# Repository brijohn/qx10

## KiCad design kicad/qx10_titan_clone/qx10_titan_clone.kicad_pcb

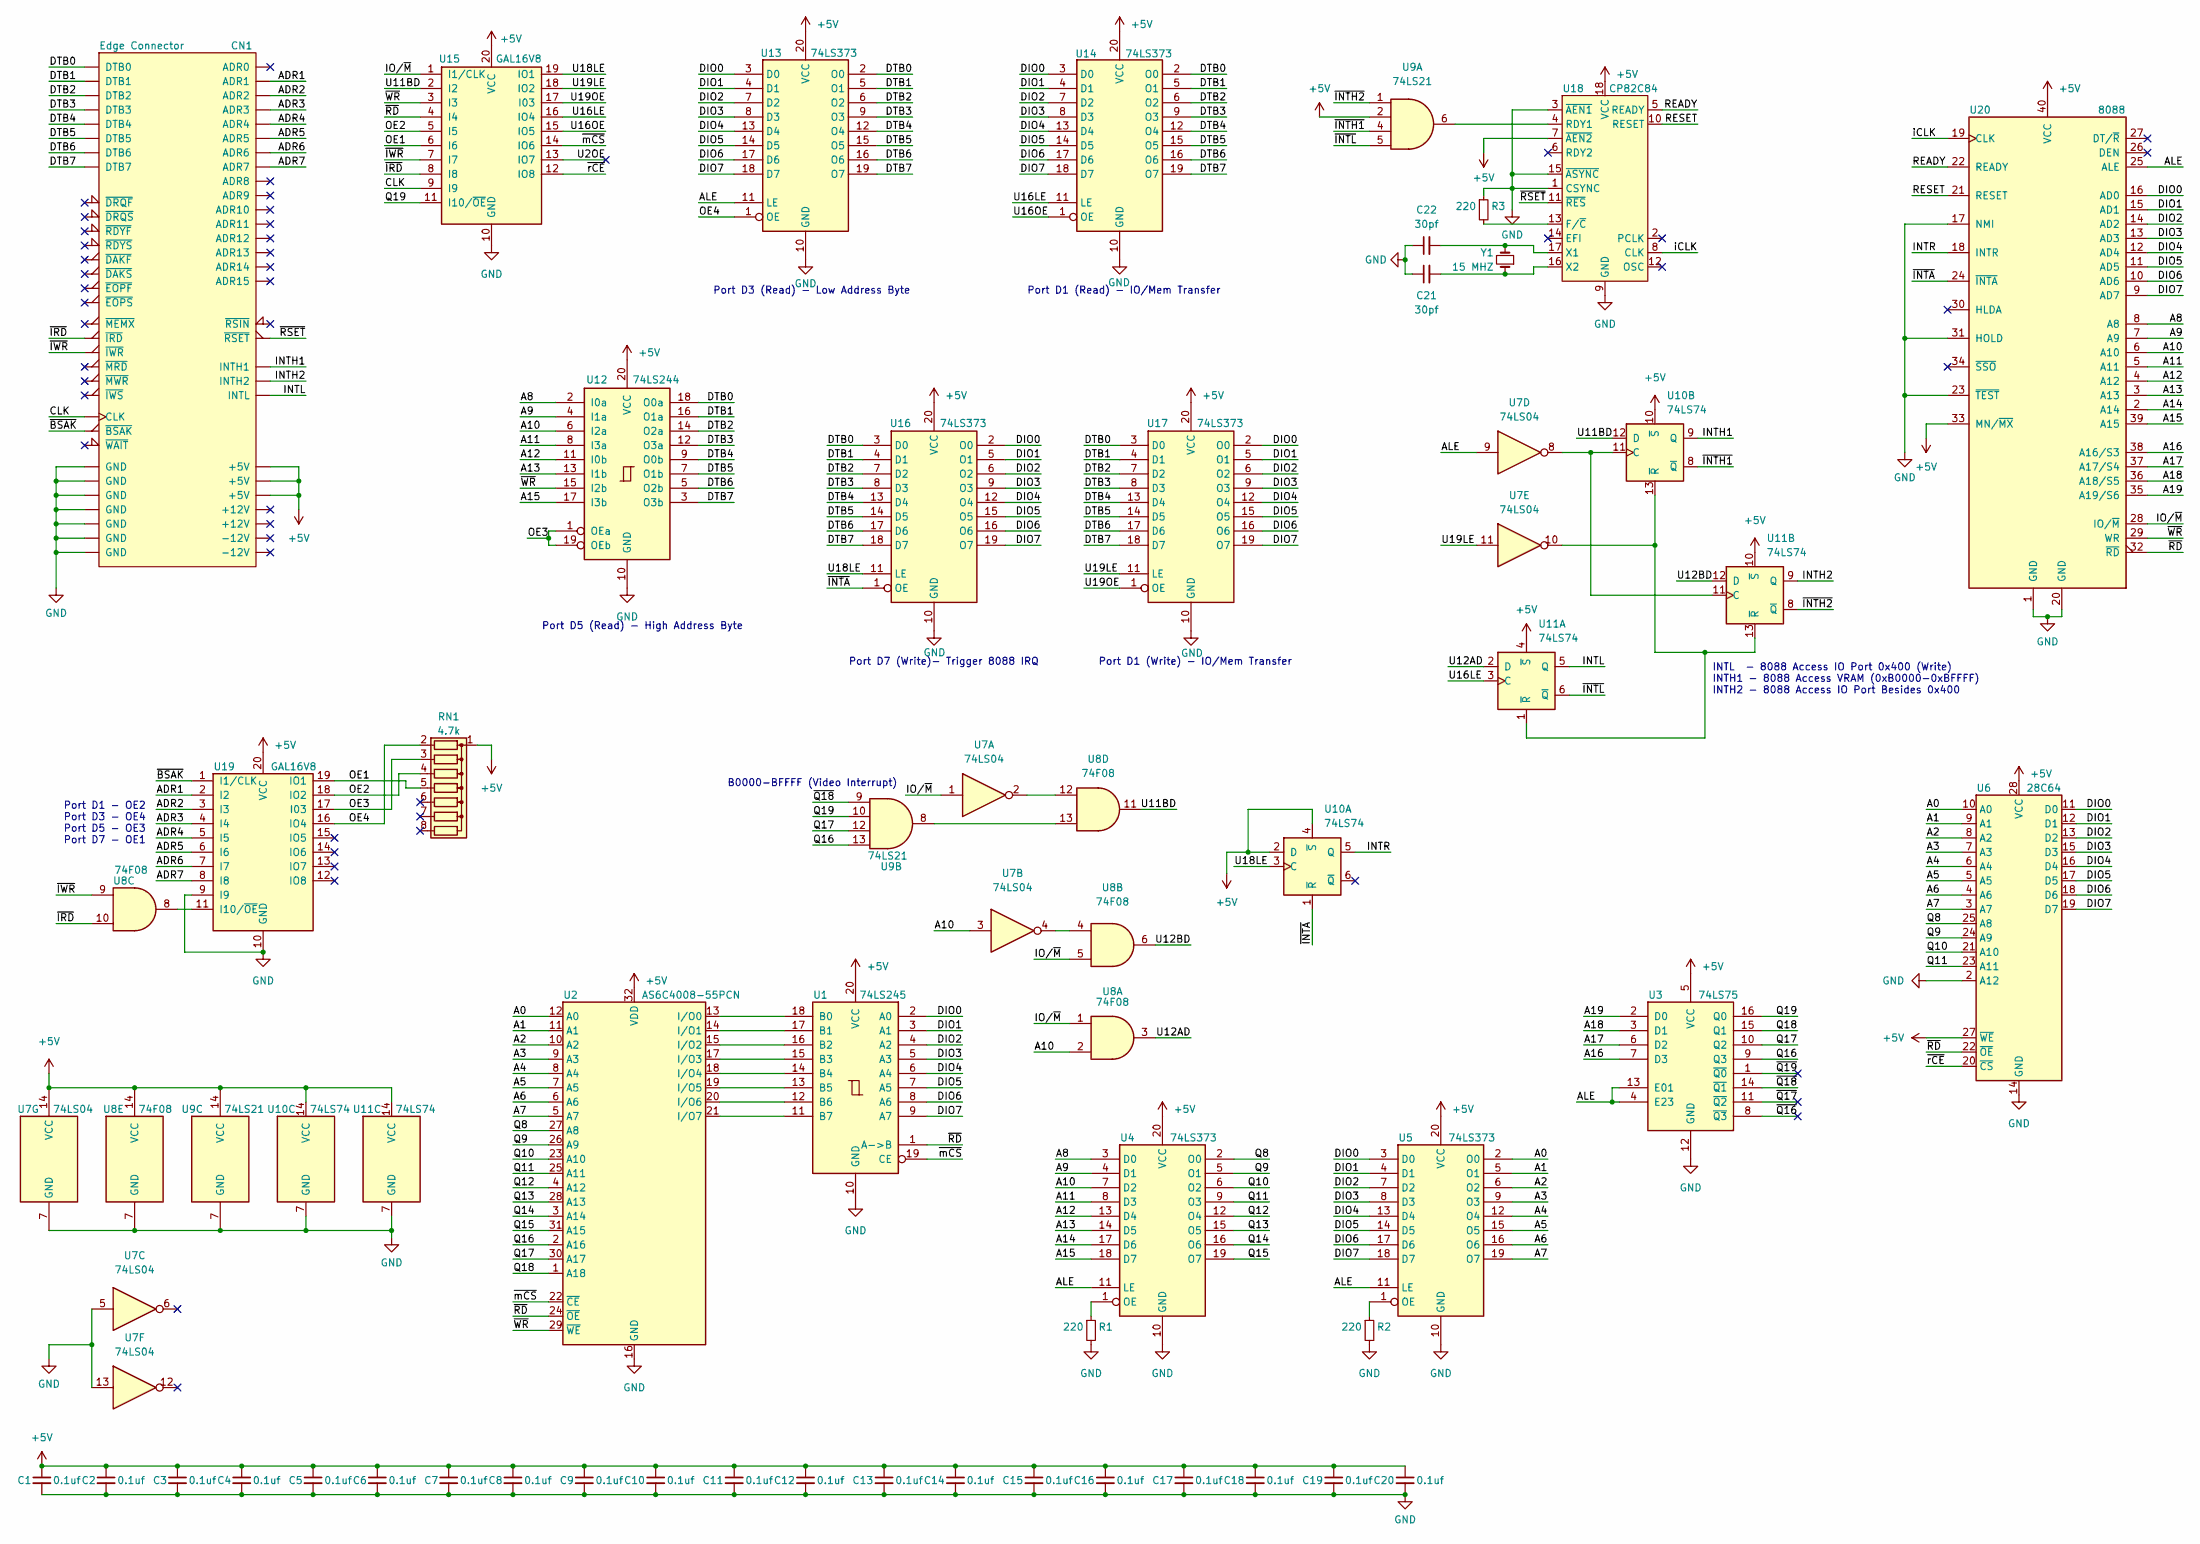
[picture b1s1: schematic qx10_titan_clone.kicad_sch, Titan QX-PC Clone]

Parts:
C1, C2, C3, C4, C5, C6, C7, C8, C9, C10, C11, C12, C13, C14, C15, C16, C17, C18, C19, C20: 0.1uf; C_Disc_D5.0mm_W2.5mm_P2.50mm; Mouser 81-RDER72A104K1S1H3A
C21, C22: 30pf; C_Disc_D5.0mm_W2.5mm_P2.50mm; Mouser 80-C315C300F3G5TA
CN1: Edge Connector; BUS_QX10
R1, R2, R3: 220; R_Axial_DIN0207_L6.3mm_D2.5mm_P10.16mm_Horizontal; Mouser 603-CFR-25JR-52220R
RN1: 4.7k; R_Array_SIP8; Mouser 652-4608X-AP1-472LF
U1: 74LS245; DIP-20_W7.62mm_Socket_LongPads; Mouser 595-SN74LS245N
U2: AS6C4008-55PCN; DIP-32_W15.24mm_Socket_LongPads; Mouser 913-AS6C4008-55PCN
U3: 74LS75; DIP-16_W7.62mm_Socket_LongPads; Mouser 595-SN74LS75N
U4, U5, U13, U14, U16, U17: 74LS373; DIP-20_W7.62mm_Socket_LongPads; Mouser 595-SN74LS373N
U6: 28C64; DIP-28_W15.24mm_Socket_LongPads; Mouser 556-AT28C64B15PU
U7: 74LS04; DIP-14_W7.62mm_Socket_LongPads; Mouser 595-SN74LS04N
U8: 74F08; DIP-14_W7.62mm_Socket_LongPads; Mouser 595-SN74F08N
U9: 74LS21; DIP-14_W7.62mm_Socket_LongPads; Mouser 595-SN74LS21N
U10, U11: 74LS74; DIP-14_W7.62mm_Socket_LongPads; Mouser 595-SN74LS74AN
U12: 74LS244; DIP-20_W7.62mm_Socket_LongPads; Mouser 595-SN74LS244N
U15, U19: GAL16V8; DIP-20_W7.62mm_Socket_LongPads; Mouser 556-AF16V8B15PU
U18: CP82C84; DIP-18_W7.62mm_Socket_LongPads
U20: 8088; DIP-40_W15.24mm_Socket_LongPads
Y1: 15 MHZ; Crystal_HC49-U_Vertical; Mouser 695-HC49US-15-U

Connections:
+5V: C1.1, C2.1, C3.1, C4.1, C5.1, C6.1, C7.1, C8.1, C9.1, C10.1, C11.1, C12.1, C13.1, C14.1, C15.1, C16.1, C17.1, C18.1, C19.1, C20.1, CN1.43 (+5V), CN1.45 (+5V), CN1.46 (+5V), RN1.1 (common), U1.20 (VCC), U2.32 (VDD), U3.5 (VCC), U4.20 (VCC), U5.20 (VCC), U6.27 (~WE), U6.28 (VCC), U7.14 (VCC), U8.14 (VCC), U9.2, U9.14 (VCC), U10.2 (D), U10.4 (~S), U10.10 (~S), U10.14 (VCC), U11.4 (~S), U11.10 (~S), U11.14 (VCC), U12.20 (VCC), U13.20 (VCC), U14.20 (VCC), U15.20 (VCC), U16.20 (VCC), U17.20 (VCC), U18.7 (~AEN2), U18.18 (VCC), U19.20 (VCC), U20.33 (MN/~MX), U20.40 (VCC)
/A0: U2.12 (A0), U5.2 (O0), U6.10 (A0)
/A1: U2.11 (A1), U5.5 (O1), U6.9 (A1)
/A2: U2.10 (A2), U5.6 (O2), U6.8 (A2)
/A3: U2.9 (A3), U5.9 (O3), U6.7 (A3)
/A4: U2.8 (A4), U5.12 (O4), U6.6 (A4)
/A5: U2.7 (A5), U5.15 (O5), U6.5 (A5)
/A6: U2.6 (A6), U5.16 (O6), U6.4 (A6)
/A7: U2.5 (A7), U5.19 (O7), U6.3 (A7)
/A8: U4.3 (D0), U12.2 (I0a), U20.8 (A8)
/A9: U4.4 (D1), U12.4 (I1a), U20.7 (A9)
/A10: U4.7 (D2), U7.3, U8.2, U12.6 (I2a), U20.6 (A10)
/A11: U4.8 (D3), U12.8 (I3a), U20.5 (A11)
/A12: U4.13 (D4), U12.11 (I0b), U20.4 (A12)
/A13: U4.14 (D5), U12.13 (I1b), U20.3 (A13)
/A14: U4.17 (D6), U20.2 (A14)
/A15: U4.18 (D7), U12.17 (I3b), U20.39 (A15)
/A16: U3.7 (D3), U20.38 (A16/S3)
/A17: U3.6 (D2), U20.37 (A17/S4)
/A18: U3.3 (D1), U20.36 (A18/S5)
/A19: U3.2 (D0), U20.35 (A19/S6)
/ADR1: CN1.14 (ADR1), U19.2 (I2)
/ADR2: CN1.15 (ADR2), U19.3 (I3)
/ADR3: CN1.16 (ADR3), U19.4 (I4)
/ADR4: CN1.17 (ADR4), U19.5 (I5)
/ADR5: CN1.18 (ADR5), U19.6 (I6)
/ADR6: CN1.19 (ADR6), U19.7 (I7)
/ADR7: CN1.20 (ADR7), U19.8 (I8)
/ALE: U3.4 (E23), U3.13 (E01), U4.11 (LE), U5.11 (LE), U7.9, U13.11 (LE), U20.25 (ALE)
/CLK: CN1.31 (CLK), U15.9 (I9)
/DIO0: U1.2 (A0), U5.3 (D0), U6.11 (D0), U13.3 (D0), U14.3 (D0), U16.2 (O0), U17.2 (O0), U20.16 (AD0)
/DIO1: U1.3 (A1), U5.4 (D1), U6.12 (D1), U13.4 (D1), U14.4 (D1), U16.5 (O1), U17.5 (O1), U20.15 (AD1)
/DIO2: U1.4 (A2), U5.7 (D2), U6.13 (D2), U13.7 (D2), U14.7 (D2), U16.6 (O2), U17.6 (O2), U20.14 (AD2)
/DIO3: U1.5 (A3), U5.8 (D3), U6.15 (D3), U13.8 (D3), U14.8 (D3), U16.9 (O3), U17.9 (O3), U20.13 (AD3)
/DIO4: U1.6 (A4), U5.13 (D4), U6.16 (D4), U13.13 (D4), U14.13 (D4), U16.12 (O4), U17.12 (O4), U20.12 (AD4)
/DIO5: U1.7 (A5), U5.14 (D5), U6.17 (D5), U13.14 (D5), U14.14 (D5), U16.15 (O5), U17.15 (O5), U20.11 (AD5)
/DIO6: U1.8 (A6), U5.17 (D6), U6.18 (D6), U13.17 (D6), U14.17 (D6), U16.16 (O6), U17.16 (O6), U20.10 (AD6)
/DIO7: U1.9 (A7), U5.18 (D7), U6.19 (D7), U13.18 (D7), U14.18 (D7), U16.19 (O7), U17.19 (O7), U20.9 (AD7)
/DTB0: CN1.3 (DTB0), U12.18 (O0a), U13.2 (O0), U14.2 (O0), U16.3 (D0), U17.3 (D0)
/DTB1: CN1.4 (DTB1), U12.16 (O1a), U13.5 (O1), U14.5 (O1), U16.4 (D1), U17.4 (D1)
/DTB2: CN1.5 (DTB2), U12.14 (O2a), U13.6 (O2), U14.6 (O2), U16.7 (D2), U17.7 (D2)
/DTB3: CN1.6 (DTB3), U12.12 (O3a), U13.9 (O3), U14.9 (O3), U16.8 (D3), U17.8 (D3)
/DTB4: CN1.7 (DTB4), U12.9 (O0b), U13.12 (O4), U14.12 (O4), U16.13 (D4), U17.13 (D4)
/DTB5: CN1.8 (DTB5), U12.7 (O1b), U13.15 (O5), U14.15 (O5), U16.14 (D5), U17.14 (D5)
/DTB6: CN1.9 (DTB6), U12.5 (O2b), U13.16 (O6), U14.16 (O6), U16.17 (D6), U17.17 (D6)
/DTB7: CN1.10 (DTB7), U12.3 (O3b), U13.19 (O7), U14.19 (O7), U16.18 (D7), U17.18 (D7)
/INTH1: CN1.40 (INTH1), U10.9 (Q)
/INTH2: CN1.41 (INTH2), U11.9 (Q)
/INTL: CN1.42 (INTL), U11.5 (Q)
/INTR: U10.5 (Q), U20.18 (INTR)
/IO/~M: U7.1, U8.1, U8.5, U15.1 (I1/CLK), U20.28 (IO/~M)
/OE1: RN1.5 (R4), U15.6 (I6), U19.19 (IO1)
/OE2: RN1.4 (R3), U15.5 (I5), U19.18 (IO2)
/OE3: RN1.3 (R2), U12.1 (OEa), U12.19 (OEb), U19.17 (I03)
/OE4: RN1.2 (R1), U13.1 (OE), U19.16 (IO4)
/Q8: U2.27 (A8), U4.2 (O0), U6.25 (A8)
/Q9: U2.26 (A9), U4.5 (O1), U6.24 (A9)
/Q10: U2.23 (A10), U4.6 (O2), U6.21 (A10)
/Q11: U2.25 (A11), U4.9 (O3), U6.23 (A11)
/Q12: U2.4 (A12), U4.12 (O4)
/Q13: U2.28 (A13), U4.15 (O5)
/Q14: U2.3 (A14), U4.16 (O6)
/Q15: U2.31 (A15), U4.19 (O7)
/Q16: U2.2 (A16), U3.9 (Q3), U9.13
/Q17: U2.30 (A17), U3.10 (Q2), U9.12
/Q18: U2.1 (A18), U3.15 (Q1)
/Q19: U3.16 (Q0), U9.10, U15.11 (I10/~OE)
/READY: U18.5 (READY), U20.22 (READY)
/RESET: U18.10 (RESET), U20.21 (RESET)
/U2OE: U15.13 (IO7)
/U11BD: U8.11, U10.12 (D), U15.2 (I2)
/U12AD: U8.3, U11.2 (D)
/U12BD: U8.6, U11.12 (D)
/U16LE: U11.3 (C), U14.11 (LE), U15.16 (IO4)
/U16OE: U14.1 (OE), U15.15 (IO5)
/U18LE: U10.3 (C), U15.19 (IO1), U16.11 (LE)
/U19LE: U7.11, U15.18 (IO2), U17.11 (LE)
/U19OE: U15.17 (I03), U17.1 (OE)
/iCLK: U18.8 (CLK), U20.19 (CLK)
/~BSAK: CN1.33 (~BSAK), U19.1 (I1/CLK)
/~INTA: U10.1 (~R), U16.1 (OE), U20.24 (~INTA)
/~INTH1: U9.4, U10.8 (~Q)
/~INTH2: U9.1, U11.8 (~Q)
/~INTL: U9.5, U11.6 (~Q)
/~IRD: CN1.35 (~IRD), U8.10, U15.8 (I8)
/~IWR: CN1.36 (~IWR), U8.9, U15.7 (I7)
/~Q16: U3.8 (~Q3)
/~Q17: U3.11 (~Q2)
/~Q18: U3.14 (~Q1), U9.9
/~Q19: U3.1 (~Q0)
/~RD: U1.1 (A->B), U2.24 (~OE), U6.22 (~OE), U15.4 (I4), U20.32 (~RD)
/~RSET: CN1.44 (~RSET), U18.11 (~RES)
/~WR: U2.29 (~WE), U12.15 (I2b), U15.3 (I3), U20.29 (WR)
/~mCS: U1.19 (CE), U2.22 (~CE), U15.14 (IO6)
/~rCE: U6.20 (~CS), U15.12 (IO8)
GND: C1.2, C2.2, C3.2, C4.2, C5.2, C6.2, C7.2, C8.2, C9.2, C10.2, C11.2, C12.2, C13.2, C14.2, C15.2, C16.2, C17.2, C18.2, C19.2, C20.2, C21.1, C22.1, CN1.1 (GND), CN1.2 (GND), CN1.29 (GND), CN1.30 (GND), CN1.32 (GND), CN1.59 (GND), CN1.60 (GND), R1.2, R2.2, R3.1, U1.10 (GND), U2.16 (GND), U3.12 (GND), U4.10 (GND), U5.10 (GND), U6.2 (A12), U6.14 (GND), U7.5, U7.7 (GND), U7.13, U8.7 (GND), U9.7 (GND), U10.7 (GND), U11.7 (GND), U12.10 (GND), U13.10 (GND), U14.10 (GND), U15.10 (GND), U16.10 (GND), U17.10 (GND), U18.1 (CSYNC), U18.3 (~AEN1), U18.9 (GND), U18.15 (~ASYNC), U19.9 (I9), U19.10 (GND), U20.1 (GND), U20.17 (NMI), U20.20 (GND), U20.23 (~TEST), U20.31 (HOLD)
unnamed: C21.2, U18.16 (X2), Y1.1
unnamed: C22.2, U18.17 (X1), Y1.2
unnamed: R1.1, U4.1 (OE)
unnamed: R2.1, U5.1 (OE)
unnamed: R3.2, U18.13 (F/~C)
unnamed: U1.11 (B7), U2.21 (I/O7)
unnamed: U1.12 (B6), U2.20 (I/O6)
unnamed: U1.13 (B5), U2.19 (I/O5)
unnamed: U1.14 (B4), U2.18 (I/O4)
unnamed: U1.15 (B3), U2.17 (I/O3)
unnamed: U1.16 (B2), U2.15 (I/O2)
unnamed: U1.17 (B1), U2.14 (I/O1)
unnamed: U1.18 (B0), U2.13 (I/O0)
unnamed: U7.2, U8.12
unnamed: U7.4, U8.4
unnamed: U8.13, U9.8
unnamed: U7.8, U10.11 (C), U11.11 (C)
unnamed: U7.10, U10.13 (~R), U11.1 (~R), U11.13 (~R)
unnamed: U9.6, U18.4 (RDY1)
unnamed: U8.8, U19.11 (I10/~OE)

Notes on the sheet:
Port D3 (Read) - Low Address Byte
INTL - 8088 Access IO Port 0x400 (Write) INTH1 - 8088 Access VRAM (0xB0000-0xBFFFF) INTH2 - 8088 Access IO Port Besides 0x400
Port D1 - OE2 Port D3 - OE4 Port D5 - OE3 Port D7 - OE1
Port D7 (Write)- Trigger 8088 IRQ
B0000-BFFFF (Video Interrupt)
Port D5 (Read) - High Address Byte
Port D1 (Read) - IO/Mem Transfer
Port D1 (Write) - IO/Mem Transfer

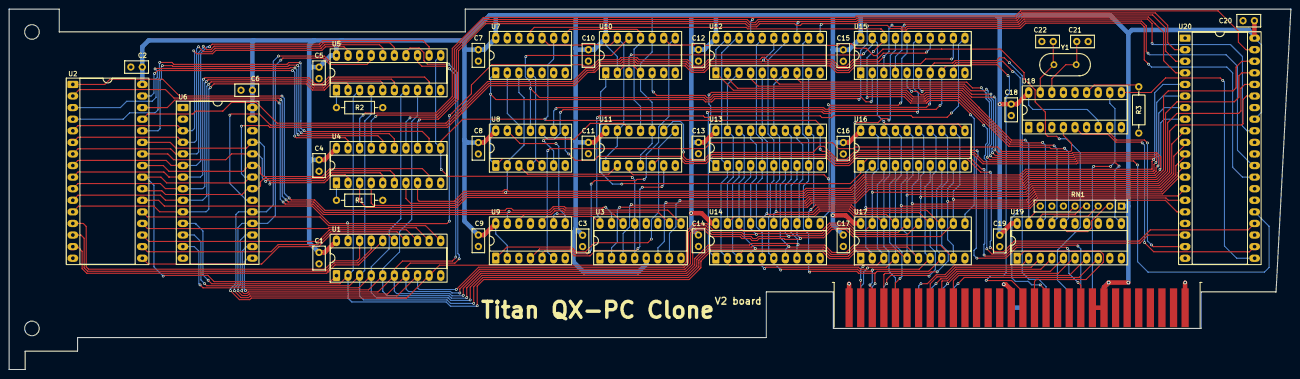
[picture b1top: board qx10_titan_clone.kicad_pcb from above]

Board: 2 copper layers, 281.0 x 79.0 mm, 50 parts (0 on the bottom side), 112 nets.

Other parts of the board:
H1, H2: MountingHole_3.2mm_M3

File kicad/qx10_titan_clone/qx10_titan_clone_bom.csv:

"Reference","Qty","Value","DNP","Footprint","Datasheet","MFR","Mouser","Firmware"
"C1,C2,C3,C4,C5,C6,C7,C8,C9,C10,C11,C12,C13,C14,C15,C16,C17,C18,C19,C20","20","0.1uf","","Capacitor_THT:C_Disc_D5.0mm_W2.5mm_P2.50mm","~","RDER72A104K1S1H03A","81-RDER72A104K1S1H3A",""
"C21,C22","2","30pf","","Capacitor_THT:C_Disc_D5.0mm_W2.5mm_P2.50mm","~","C315C300F3G5TA","80-C315C300F3G5TA",""
"R1,R2,R3","3","220","","Resistor_THT:R_Axial_DIN0207_L6.3mm_D2.5mm_P10.16mm_Horizontal","~","CFR-25JR-52-220R","603-CFR-25JR-52220R",""
"RN1","1","4.7k","","Resistor_THT:R_Array_SIP8","http://www.vishay.com/docs/31509/csc.pdf","4608X-AP1-472LF","652-4608X-AP1-472LF",""
"U1","1","74LS245","","Package_DIP:DIP-20_W7.62mm_Socket_LongPads","http://www.ti.com/lit/gpn/sn74LS245","SN74LS245N","595-SN74LS245N",""
"U2","1","AS6C4008-55PCN","","Package_DIP:DIP-32_W15.24mm_Socket_LongPads","https://www.alliancememory.com/wp-content/uploads/pdf/AS6C4008.pdf","AS6C4008-55PCN","913-AS6C4008-55PCN",""
"U3","1","74LS75","","Package_DIP:DIP-16_W7.62mm_Socket_LongPads","http://www.ti.com/lit/gpn/sn74LS75","SN74LS75N","595-SN74LS75N",""
"U4,U5,U13,U14,U16,U17","6","74LS373","","Package_DIP:DIP-20_W7.62mm_Socket_LongPads","http://www.ti.com/lit/gpn/sn74LS373","SN74LS373N","595-SN74LS373N",""
"U6","1","28C64","","Package_DIP:DIP-28_W15.24mm_Socket_LongPads","https://www.mouser.com/datasheet/2/268/doc0270-1108115.pdf","AT28C64B-15PU","556-AT28C64B15PU","QXPC.ROM"
"U7","1","74LS04","","Package_DIP:DIP-14_W7.62mm_Socket_LongPads","http://www.ti.com/lit/gpn/sn74LS04","SN74LS04N","595-SN74LS04N",""
"U8","1","74F08","","Package_DIP:DIP-14_W7.62mm_Socket_LongPads","http://www.ti.com/lit/gpn/sn74LS08","SN74F08N","595-SN74F08N",""
"U9","1","74LS21","","Package_DIP:DIP-14_W7.62mm_Socket_LongPads","http://www.ti.com/lit/gpn/sn74LS21","SN74LS21N","595-SN74LS21N",""
"U10,U11","2","74LS74","","Package_DIP:DIP-14_W7.62mm_Socket_LongPads","74xx/74hc_hct74.pdf","SN74LS74AN","595-SN74LS74AN",""
"U12","1","74LS244","","Package_DIP:DIP-20_W7.62mm_Socket_LongPads","http://www.ti.com/lit/ds/symlink/sn74ls244.pdf","SN74LS244N","595-SN74LS244N",""
"U15","1","GAL16V8","","Package_DIP:DIP-20_W7.62mm_Socket_LongPads","https://www.mouser.com/datasheet/2/268/Atmel_0364_PLD_ATF16V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","ATF16V8B-15PU","556-AF16V8B15PU","TITAN.JED"
"U19","1","GAL16V8","","Package_DIP:DIP-20_W7.62mm_Socket_LongPads","https://www.mouser.com/datasheet/2/268/Atmel_0364_PLD_ATF16V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","ATF16V8B-15PU","556-AF16V8B15PU","IODECODE.JED"
"Y1","1","15 MHZ","","Crystal:Crystal_HC49-U_Vertical","https://www.mouser.com/datasheet/2/77/HC_49_U_S_E-1131675.pdf","HC-49/U-S15000000ABJB","695-HC49US-15-U",""

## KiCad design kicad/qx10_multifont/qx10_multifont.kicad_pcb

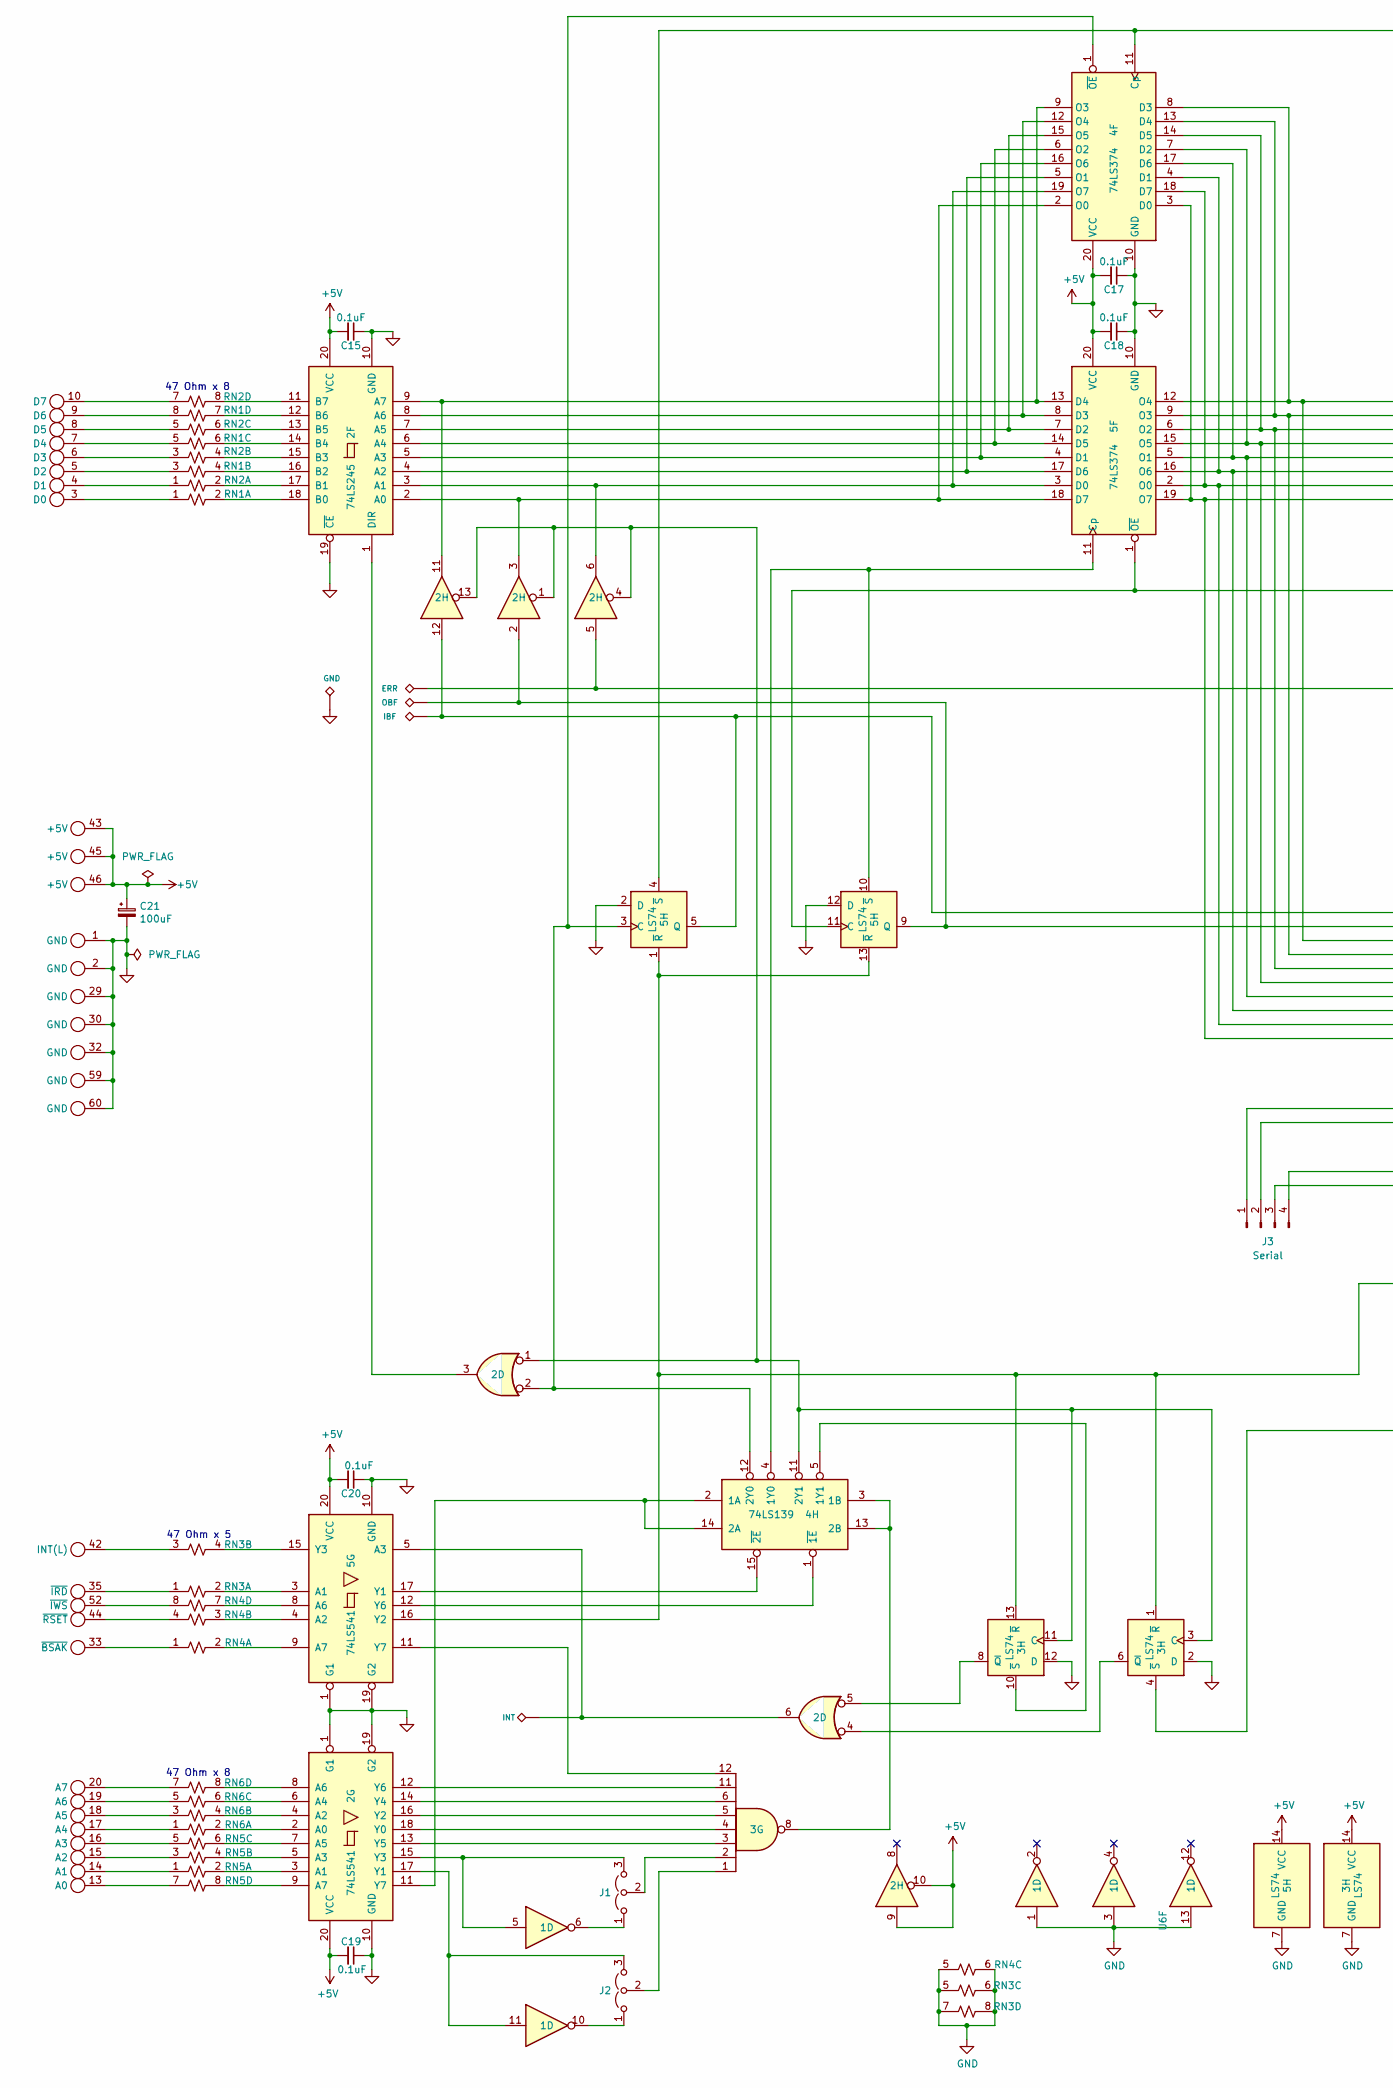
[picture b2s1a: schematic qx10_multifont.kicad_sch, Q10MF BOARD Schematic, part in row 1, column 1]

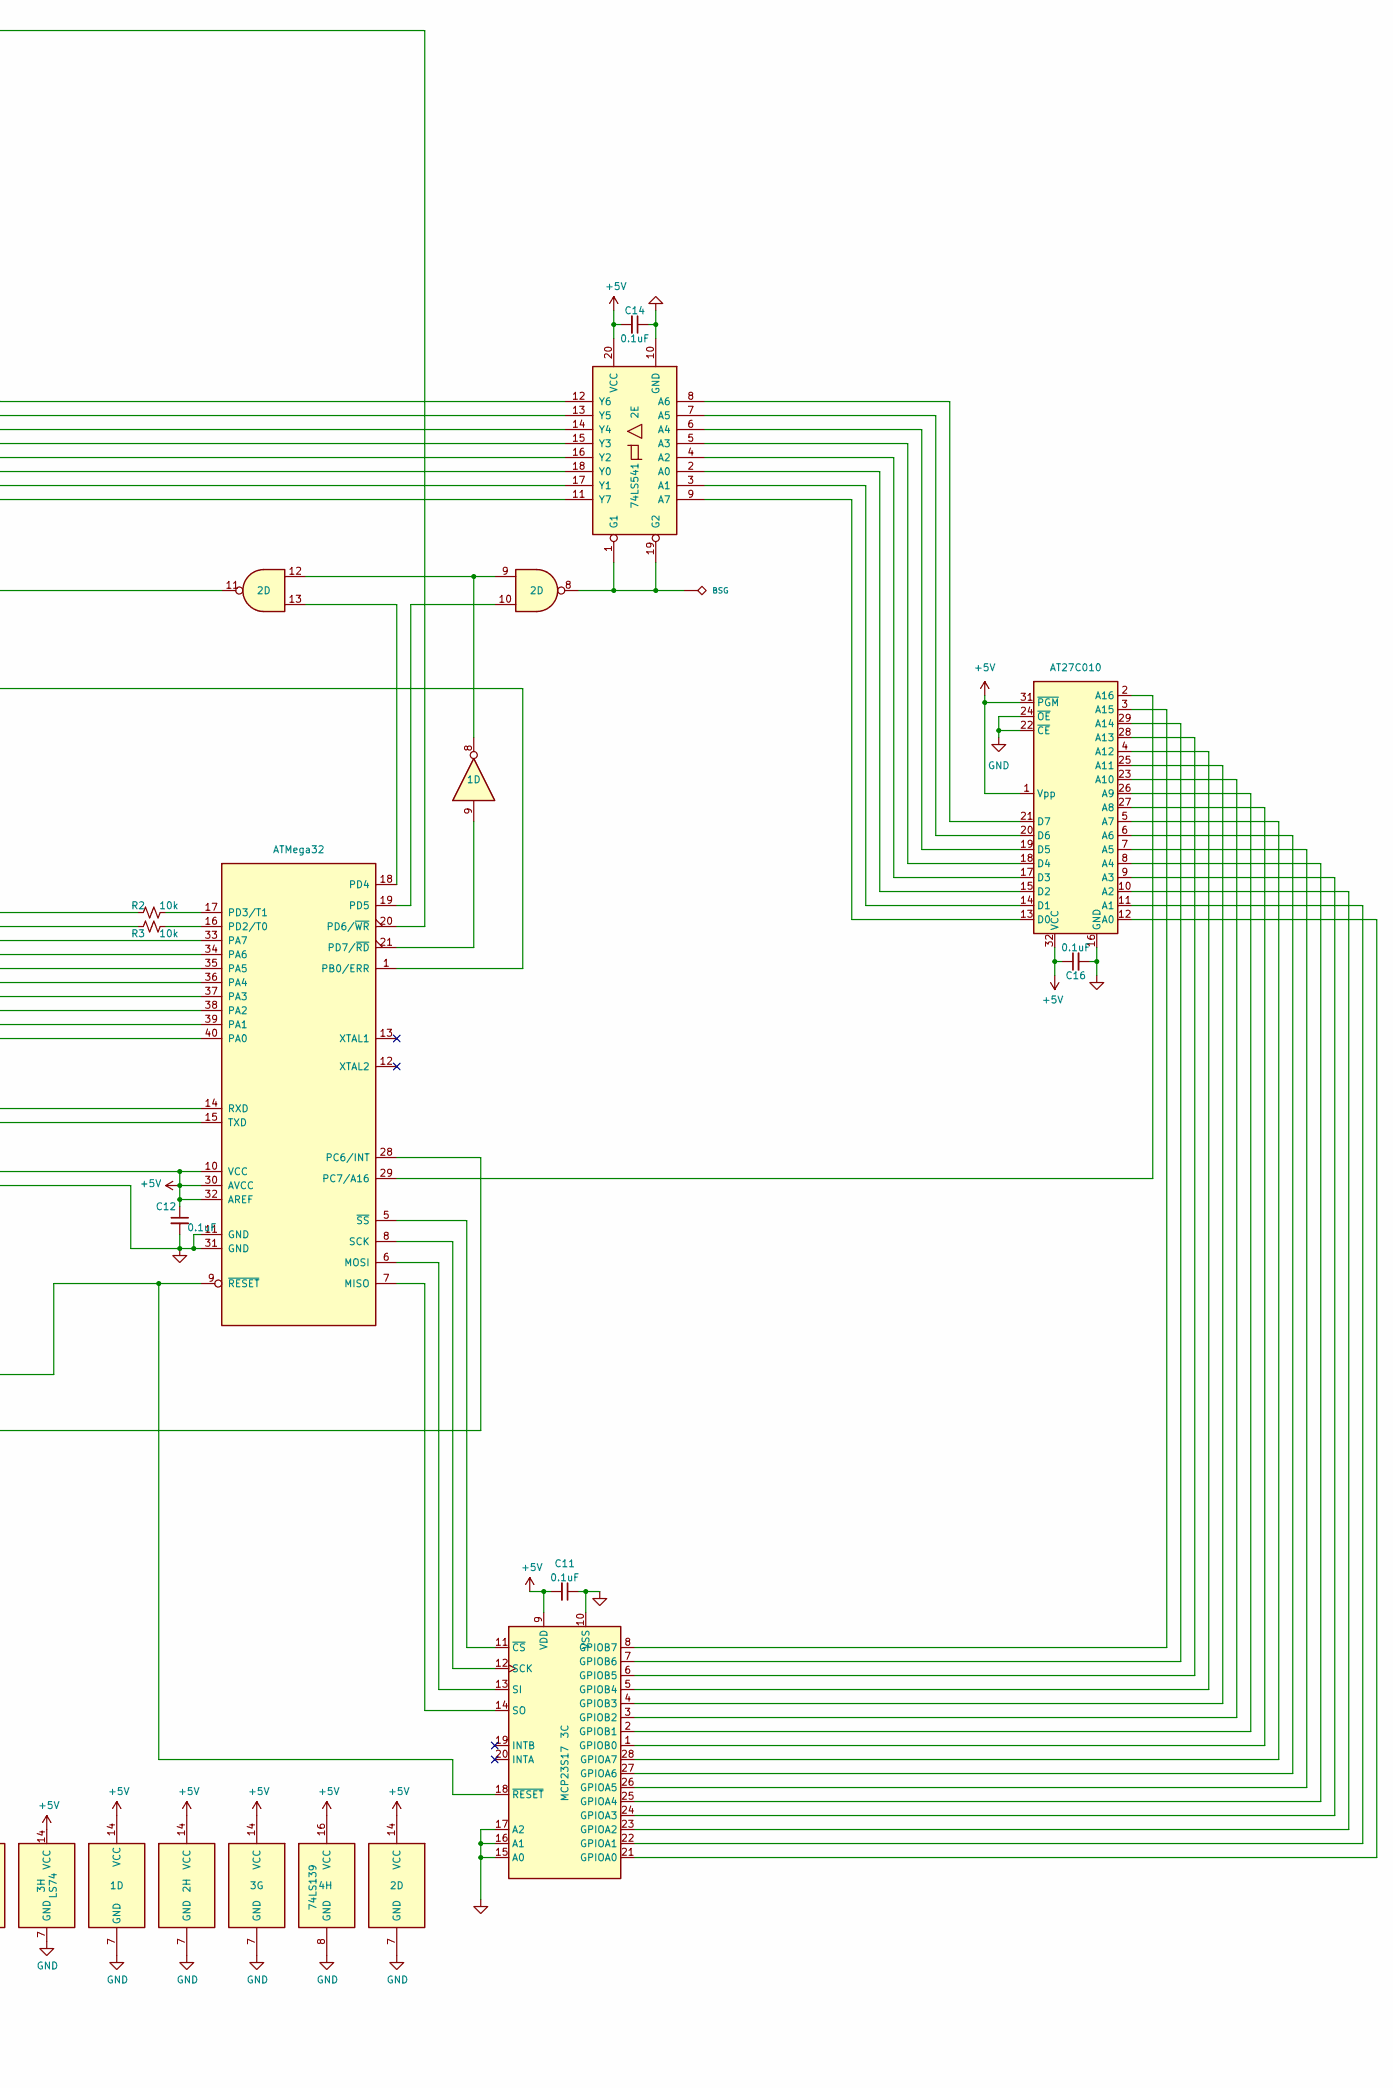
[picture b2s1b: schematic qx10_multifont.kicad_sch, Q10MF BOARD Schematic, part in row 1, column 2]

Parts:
C11, C12, C14, C15, C16, C17, C18, C19, C20: 0.1uF; C_Disc_D5.0mm_W2.5mm_P2.50mm; Digikey 56-K104K15X7RF5UL2CT-ND
C21: 100uF; CP_Radial_D6.3mm_P2.50mm; Digikey 399-18280-1-ND
J1, J2: Jumper_3_Open; PinHeader_1x03_P2.54mm_Vertical
J3: Serial; PinHeader_1x04_P2.54mm_Vertical
R2, R3: 10k; R_Axial_DIN0207_L6.3mm_D2.5mm_P10.16mm_Horizontal; Digikey 13-MFR-25FRF52-10KCT-ND
RN1, RN2, RN3, RN4, RN5, RN6: R_Pack04_Split; R_Array_SIP8; Digikey 4608X-2-470LF-ND
TP1: ERR; TestPoint_1.1mm
TP2: OBF; TestPoint_1.1mm
TP3: IBF; TestPoint_1.1mm
TP4: INT; TestPoint_1.1mm
TP5: GND; TestPoint_1.1mm
TP6: BSG; TestPoint_1.1mm
U1: 74LS245; DIP-20_W7.62mm_Socket; Digikey 296-1655-5-ND
U2, U3, U17: 74LS541; DIP-20_W7.62mm_Socket; Digikey 296-1666-5-ND
U4: 74LS125; DIP-14_W7.62mm_Socket; Digikey 296-1638-5-ND
U5: 74LS00; DIP-14_W7.62mm_Socket; Digikey 296-1626-ND
U6: 74LS04; DIP-14_W7.62mm_Socket; Digikey 296-1629-5-ND
U7, U10: LS74; DIP-14_W7.62mm_Socket; Digikey 296-1668-5-ND
U8: 74LS30; DIP-14_W7.62mm_Socket; Digikey 296-3693-5-ND
U9: 74LS139; DIP-16_W7.62mm_Socket; Digikey 296-1640-5-ND
U12, U13: 74LS374; DIP-20_W7.62mm_Socket; Digikey 296-1662-5-ND
U16: MCP23S17; DIP-24_W15.24mm_Socket
U26: AT27C010; DIP-28_W15.24mm_Socket; Digikey AT27C010-70PU-ND
U27: ATMega32; DIP-40_W15.24mm_Socket
X1: EdgeConn; BUS_QX10

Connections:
+5V: C11.2, C12.1, C14.2, C15.2, C16.1, C17.2, C18.2, C19.2, C20.2, C21.1, J3.4, U1.20 (VCC), U2.20 (VCC), U3.20 (VCC), U4.9, U4.10, U4.14 (VCC), U5.14 (VCC), U6.14 (VCC), U7.14 (VCC), U8.14 (VCC), U9.16 (VCC), U10.14 (VCC), U12.20 (VCC), U13.20 (VCC), U16.9 (VDD), U17.20 (VCC), U26.1 (Vpp), U26.31 (~PGM), U26.32 (VCC), U27.10 (VCC), U27.30 (AVCC), U27.32 (AREF), X1.43 (+5V), X1.45 (+5V), X1.46 (+5V)
GND: C11.1, C12.2, C14.1, C15.1, C16.2, C17.1, C18.1, C19.1, C20.1, C21.2, J3.3, RN3.5 (R3.1), RN3.6 (R3.2), RN3.7 (R4.1), RN3.8 (R4.2), RN4.5 (R3.1), RN4.6 (R3.2), TP5.1, U1.10 (GND), U1.19 (~CE), U2.1 (G1), U2.10 (GND), U2.19 (G2), U3.1 (G1), U3.10 (GND), U3.19 (G2), U4.7 (GND), U5.7 (GND), U6.1, U6.3, U6.7 (GND), U6.13, U7.2 (D), U7.7 (GND), U7.12 (D), U8.7 (GND), U9.8 (GND), U10.2 (D), U10.7 (GND), U10.12 (D), U12.10 (GND), U13.10 (GND), U16.10 (VSS), U16.15 (A0), U16.16 (A1), U16.17 (A2), U17.10 (GND), U26.16 (GND), U26.22 (~CE), U26.24 (~OE), U27.11 (GND), U27.31 (GND), X1.1 (GND), X1.2 (GND), X1.29 (GND), X1.30 (GND), X1.32 (GND), X1.59 (GND), X1.60 (GND)
unnamed: J1.1 (A), U6.6
unnamed: J1.3 (B), U3.15 (Y3), U6.5
unnamed: J1.2 (C), U8.2
unnamed: J2.1 (A), U6.10
unnamed: J2.3 (B), U3.17 (Y1), U6.11
unnamed: J2.2 (C), U8.1
unnamed: J3.1, U27.14 (RXD)
unnamed: J3.2, U27.15 (TXD)
unnamed: RN1.1 (R1.1), X1.3 (D0)
unnamed: RN1.2 (R1.2), U1.18 (B0)
unnamed: RN1.3 (R2.1), X1.5 (D2)
unnamed: RN1.4 (R2.2), U1.16 (B2)
unnamed: RN1.5 (R3.1), X1.7 (D4)
unnamed: RN1.6 (R3.2), U1.14 (B4)
unnamed: RN1.7 (R4.1), U1.12 (B6)
unnamed: RN1.8 (R4.2), X1.9 (D6)
unnamed: RN2.1 (R1.1), X1.4 (D1)
unnamed: RN2.2 (R1.2), U1.17 (B1)
unnamed: RN2.3 (R2.1), X1.6 (D3)
unnamed: RN2.4 (R2.2), U1.15 (B3)
unnamed: RN2.5 (R3.1), X1.8 (D5)
unnamed: RN2.6 (R3.2), U1.13 (B5)
unnamed: RN2.7 (R4.1), X1.10 (D7)
unnamed: RN2.8 (R4.2), U1.11 (B7)
unnamed: RN3.1 (R1.1), X1.35 (~IRD)
unnamed: RN3.2 (R1.2), U2.3 (A1)
unnamed: RN3.3 (R2.1), X1.42 (INT(L))
unnamed: RN3.4 (R2.2), U2.15 (Y3)
unnamed: RN4.1 (R1.1), X1.33 (~BSAK)
unnamed: RN4.2 (R1.2), U2.9 (A7)
unnamed: RN4.3 (R2.1), U2.4 (A2)
unnamed: RN4.4 (R2.2), X1.44 (~RSET)
unnamed: RN4.7 (R4.1), U2.8 (A6)
unnamed: RN4.8 (R4.2), X1.52 (~IWS)
unnamed: RN5.1 (R1.1), X1.14 (A1)
unnamed: RN5.2 (R1.2), U3.3 (A1)
unnamed: RN5.3 (R2.1), X1.15 (A2)
unnamed: RN5.4 (R2.2), U3.5 (A3)
unnamed: RN5.5 (R3.1), X1.16 (A3)
unnamed: RN5.6 (R3.2), U3.7 (A5)
unnamed: RN5.7 (R4.1), X1.13 (A0)
unnamed: RN5.8 (R4.2), U3.9 (A7)
unnamed: RN6.1 (R1.1), X1.17 (A4)
unnamed: RN6.2 (R1.2), U3.2 (A0)
unnamed: RN6.3 (R2.1), X1.18 (A5)
unnamed: RN6.4 (R2.2), U3.4 (A2)
unnamed: RN6.5 (R3.1), X1.19 (A6)
unnamed: RN6.6 (R3.2), U3.6 (A4)
unnamed: RN6.7 (R4.1), X1.20 (A7)
unnamed: RN6.8 (R4.2), U3.8 (A6)
unnamed: U1.2 (A0), U4.3, U12.2 (O0), U13.18 (D7)
unnamed: U1.3 (A1), U4.6, U12.19 (O7), U13.3 (D0)
unnamed: U1.4 (A2), U12.5 (O1), U13.17 (D6)
unnamed: U1.5 (A3), U12.16 (O6), U13.4 (D1)
unnamed: U1.6 (A4), U12.6 (O2), U13.14 (D5)
unnamed: U1.7 (A5), U12.15 (O5), U13.7 (D2)
unnamed: U1.8 (A6), U12.12 (O4), U13.8 (D3)
unnamed: U1.9 (A7), U4.11, U12.9 (O3), U13.13 (D4)
unnamed: U1.1 (DIR), U5.3
unnamed: TP4.1, U2.5 (A3), U5.6
unnamed: U2.17 (Y1), U9.15 (~2E)
unnamed: U2.12 (Y6), U9.1 (~1E)
unnamed: U2.11 (Y7), U8.12
unnamed: U3.18 (Y0), U8.4
unnamed: U3.16 (Y2), U8.5
unnamed: U3.14 (Y4), U8.6
unnamed: U3.13 (Y5), U8.3
unnamed: U3.12 (Y6), U8.11
unnamed: U3.11 (Y7), U9.2 (1A), U9.14 (2A)
unnamed: U5.9, U5.12, U6.8
unnamed: R2.2, TP3.1, U4.12, U7.5 (Q)
unnamed: R3.2, TP2.1, U4.2, U7.9 (Q)
unnamed: U8.8, U9.3 (1B), U9.13 (2B)
unnamed: U4.1, U4.4, U4.13, U5.1, U9.11 (2Y1), U10.3 (C), U10.11 (C)
unnamed: U5.4, U10.6 (~Q)
unnamed: U2.16 (Y2), U7.1 (~R), U7.13 (~R), U10.1 (~R), U10.13 (~R), U16.18 (~RESET), U27.9 (~RESET)
unnamed: U10.4 (~S), U27.28 (PC6/INT)
unnamed: U5.5, U10.8 (~Q)
unnamed: U9.5 (1Y1), U10.10 (~S)
unnamed: U7.4 (~S), U12.11 (Cp), U27.20 (PD6/~WR)
unnamed: U12.3 (D0), U13.19 (O7), U17.11 (Y7), U27.40 (PA0)
unnamed: U12.4 (D1), U13.16 (O6), U17.18 (Y0), U27.38 (PA2)
unnamed: U12.7 (D2), U13.15 (O5), U17.15 (Y3), U27.36 (PA4)
unnamed: U12.8 (D3), U13.12 (O4), U17.12 (Y6), U27.33 (PA7)
unnamed: U12.13 (D4), U13.9 (O3), U17.13 (Y5), U27.34 (PA6)
unnamed: U12.14 (D5), U13.6 (O2), U17.14 (Y4), U27.35 (PA5)
unnamed: U12.17 (D6), U13.5 (O1), U17.16 (Y2), U27.37 (PA3)
unnamed: U12.18 (D7), U13.2 (O0), U17.17 (Y1), U27.39 (PA1)
unnamed: U5.2, U7.3 (C), U9.12 (2Y0), U12.1 (~OE)
unnamed: U7.10 (~S), U9.4 (1Y0), U13.11 (Cp)
unnamed: U5.11, U7.11 (C), U13.1 (~OE)
unnamed: U16.21 (GPIOA0), U26.12 (A0)
unnamed: U16.22 (GPIOA1), U26.11 (A1)
unnamed: U16.23 (GPIOA2), U26.10 (A2)
unnamed: U16.24 (GPIOA3), U26.9 (A3)
unnamed: U16.25 (GPIOA4), U26.8 (A4)
unnamed: U16.26 (GPIOA5), U26.7 (A5)
unnamed: U16.27 (GPIOA6), U26.6 (A6)
unnamed: U16.28 (GPIOA7), U26.5 (A7)
unnamed: U16.1 (GPIOB0), U26.27 (A8)
unnamed: U16.2 (GPIOB1), U26.26 (A9)
unnamed: U16.3 (GPIOB2), U26.23 (A10)
unnamed: U16.4 (GPIOB3), U26.25 (A11)
unnamed: U16.5 (GPIOB4), U26.4 (A12)
unnamed: U16.6 (GPIOB5), U26.28 (A13)
unnamed: U16.7 (GPIOB6), U26.29 (A14)
unnamed: U16.8 (GPIOB7), U26.3 (A15)
unnamed: U16.12 (SCK), U27.8 (SCK)
unnamed: U16.13 (SI), U27.6 (MOSI)
unnamed: U16.14 (SO), U27.7 (MISO)
unnamed: U16.11 (~CS), U27.5 (~SS)
unnamed: U17.2 (A0), U26.15 (D2)
unnamed: U17.3 (A1), U26.14 (D1)
unnamed: U17.4 (A2), U26.17 (D3)
unnamed: U17.5 (A3), U26.18 (D4)
unnamed: U17.6 (A4), U26.19 (D5)
unnamed: U17.7 (A5), U26.20 (D6)
unnamed: U17.8 (A6), U26.21 (D7)
unnamed: U17.9 (A7), U26.13 (D0)
unnamed: TP6.1, U5.8, U17.1 (G1), U17.19 (G2)
unnamed: U26.2 (A16), U27.29 (PC7/A16)
unnamed: TP1.1, U4.5, U27.1 (PB0/ERR)
unnamed: R3.1, U27.16 (PD2/T0)
unnamed: R2.1, U27.17 (PD3/T1)
unnamed: U5.13, U27.18 (PD4)
unnamed: U5.10, U27.19 (PD5)
unnamed: U6.9, U27.21 (PD7/~RD)

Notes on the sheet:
47 Ohm x 5
47 Ohm x 8

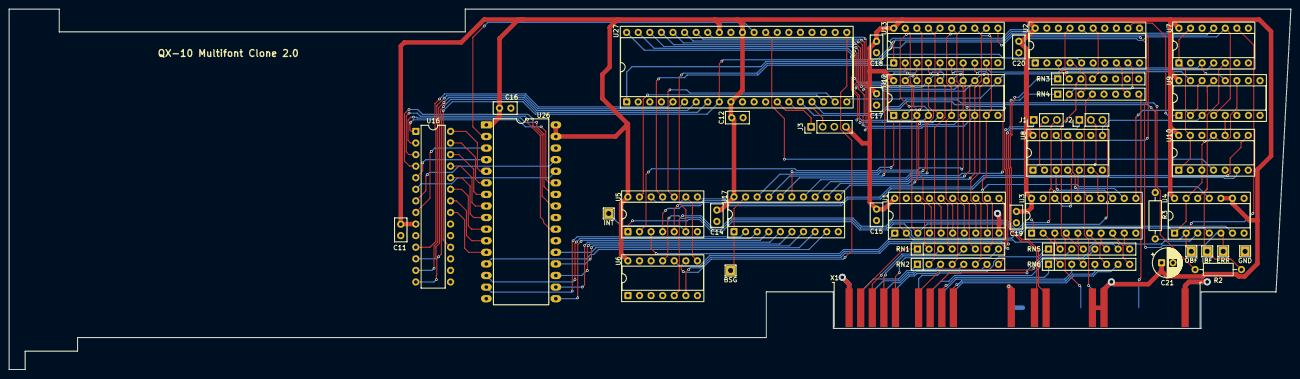
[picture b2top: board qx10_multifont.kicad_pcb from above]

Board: 2 copper layers, 281.0 x 79.0 mm, 44 parts (0 on the bottom side), 129 nets.

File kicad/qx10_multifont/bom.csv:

"Reference","Value","Datasheet","Footprint","Qty","DNP","MFR","Digikey"
"C11,C12,C14,C15,C16,C17,C18,C19,C20","0.1uF","~","Capacitor_THT:C_Disc_D5.0mm_W2.5mm_P2.50mm","9","","K104K15X7RF5UL2","56-K104K15X7RF5UL2CT-ND"
"C21","100uF","~","Capacitor_THT:CP_Radial_D6.3mm_P2.50mm","1","","ESS107M016AE2EA","399-18280-1-ND"
"J1,J2","Jumper_3_Open","~","Connector_PinHeader_2.54mm:PinHeader_1x03_P2.54mm_Vertical","2","","68001-103HLF","609-3468-ND"
"J3","Serial","~","Connector_PinHeader_2.54mm:PinHeader_1x04_P2.54mm_Vertical","1","","68001-104HLF ","609-3271-ND"
"R2,R3","10k","~","Resistor_THT:R_Axial_DIN0207_L6.3mm_D2.5mm_P10.16mm_Horizontal","2","","MFR-25FRF52-10K","13-MFR-25FRF52-10KCT-ND"
"RN1,RN2,RN3,RN4,RN5,RN6","R_Pack04_Split","~","Resistor_THT:R_Array_SIP8","6","","4608X-102-470LF","4608X-2-470LF-ND"
"U1","74LS245","http://www.ti.com/lit/gpn/sn74LS245","Package_DIP:DIP-20_W7.62mm_Socket","1","","SN74LS245N","296-1655-5-ND"
"U2,U3,U17","74LS541","http://www.ti.com/lit/gpn/sn74LS541","Package_DIP:DIP-20_W7.62mm_Socket","3","","SN74LS541N","296-1666-5-ND"
"U4","74LS125","http://www.ti.com/lit/gpn/sn74LS125","Package_DIP:DIP-14_W7.62mm_Socket","1","","SN74LS125AN","296-1638-5-ND"
"U5","74LS00","http://www.ti.com/lit/gpn/sn74ls00","Package_DIP:DIP-14_W7.62mm_Socket","1","","SN74LS00N","296-1626-ND"
"U6","74LS04","http://www.ti.com/lit/gpn/sn74LS04","Package_DIP:DIP-14_W7.62mm_Socket","1","","SN74LS04N","296-1629-5-ND"
"U7,U10","LS74","74xx/74hc_hct74.pdf","Package_DIP:DIP-14_W7.62mm_Socket","2","","SN74LS74AN","296-1668-5-ND"
"U8","74LS30","http://www.ti.com/lit/gpn/sn74LS30","Package_DIP:DIP-14_W7.62mm_Socket","1","","SN74LS30N","296-3693-5-ND"
"U9","74LS139","http://www.ti.com/lit/ds/symlink/sn74ls139a.pdf","Package_DIP:DIP-16_W7.62mm_Socket","1","","SN74LS139AN","296-1640-5-ND"
"U12,U13","74LS374","http://www.ti.com/lit/gpn/sn74LS374","Package_DIP:DIP-20_W7.62mm_Socket","2","","SN74LS374N","296-1662-5-ND"
"U16","MCP23S17","","Package_DIP:DIP-24_W15.24mm_Socket","1","","MCP23S17-E/SP","MCP23S17-E/SP-ND"
"U26","AT27C010","","Package_DIP:DIP-28_W15.24mm_Socket","1","","AT27C010-70PU","AT27C010-70PU-ND"
"U27","ATMega32","","Package_DIP:DIP-40_W15.24mm_Socket","1","","ATMEGA32A-PU","ATMEGA32A-PU-ND"
